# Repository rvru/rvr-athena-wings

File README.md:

# RVR Athena Wing Board
**Contributor(s):** Ethan Peck

**Contact(s):** edp2@rice.edu

## Overview
Wing boards will be a collection of boards that will expand the functionality of the base Athena Board in a variety of ways. Oscilloscopes, function generators, motor drivers, various sensors, and displays are some of the many boards planned for the future.

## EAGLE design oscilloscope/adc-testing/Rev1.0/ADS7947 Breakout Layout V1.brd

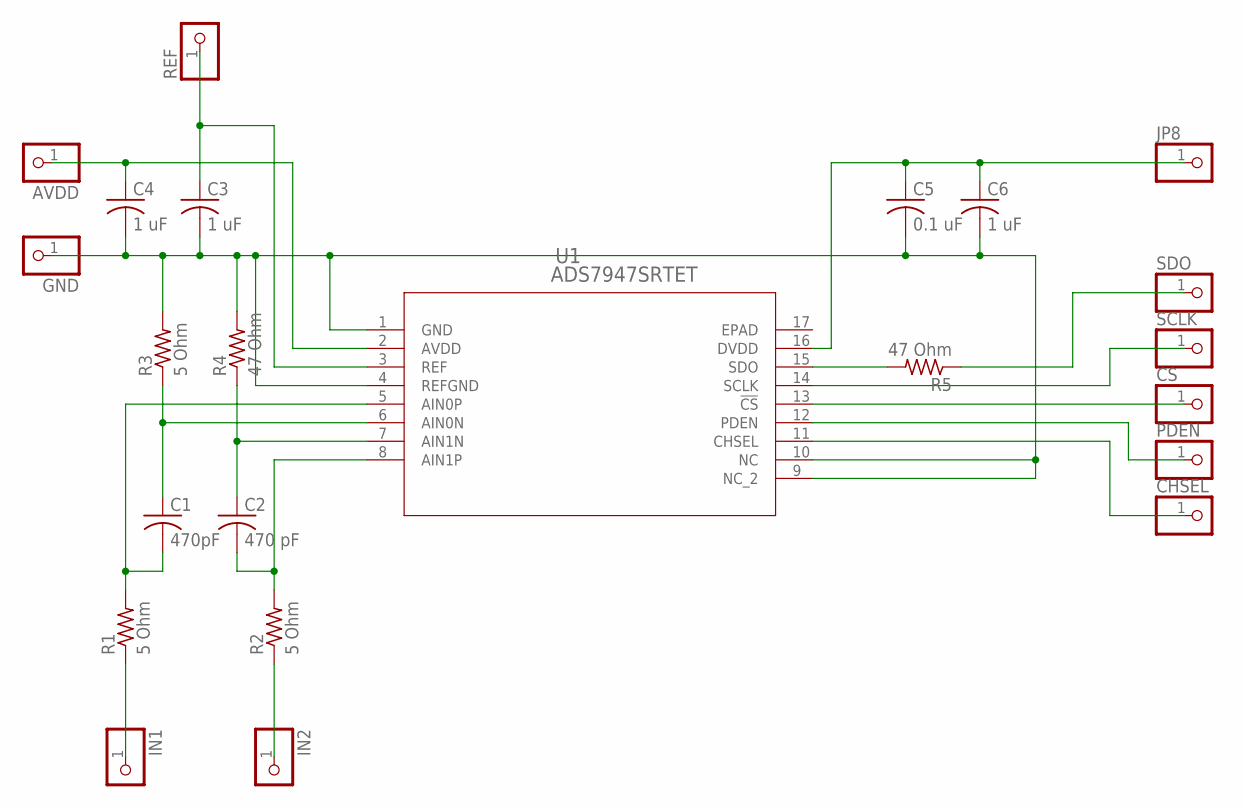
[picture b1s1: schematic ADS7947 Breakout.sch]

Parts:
AVDD: PINHD-1X1; 1X01
C1: 470pF; C1206
C2: 470 pF; C1206
C3, C4, C6: 1 uF; C1206
C5: 0.1 uF; C1206
CHSEL: PINHD-1X1; 1X01
CS: PINHD-1X1; 1X01
GND: PINHD-1X1; 1X01
IN1, IN2: PINHD-1X1; 1X01
JP8: PINHD-1X1; 1X01
PDEN: PINHD-1X1; 1X01
R1, R2, R3: 5 Ohm; R1206
R4, R5: 47 Ohm; R1206
REF: PINHD-1X1; 1X01
SCLK: PINHD-1X1; 1X01
SDO: PINHD-1X1; 1X01
U1: ADS7947SRTET; RTE16_1P7X1P7

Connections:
EPAD: U1.17 (EPAD)
GND: C3.2, C4.2, C5.2, C6.2, GND.1, R3.2, R4.2, U1.1 (GND), U1.4 (REFGND), U1.9 (NC_2), U1.10 (NC)
unnamed: IN2.1, R2.1
unnamed: C2.2, R2.2, U1.8 (AIN1P)
unnamed: C1.2, R1.2, U1.5 (AIN0P)
unnamed: IN1.1, R1.1
unnamed: C2.1, R4.1, U1.7 (AIN1N)
unnamed: C1.1, R3.1, U1.6 (AIN0N)
unnamed: C3.1, REF.1, U1.3 (REF)
unnamed: AVDD.1, C4.1, U1.2 (AVDD)
unnamed 13: C5.1, C6.1, JP8.1, U1.16 (DVDD); also elsewhere on the board
unnamed: R5.2, U1.15 (SDO)
unnamed: R5.1, SDO.1
unnamed: SCLK.1, U1.14 (SCLK)
unnamed: CS.1, U1.13 (!CS)
unnamed: PDEN.1, U1.12 (PDEN)
unnamed: CHSEL.1, U1.11 (CHSEL)

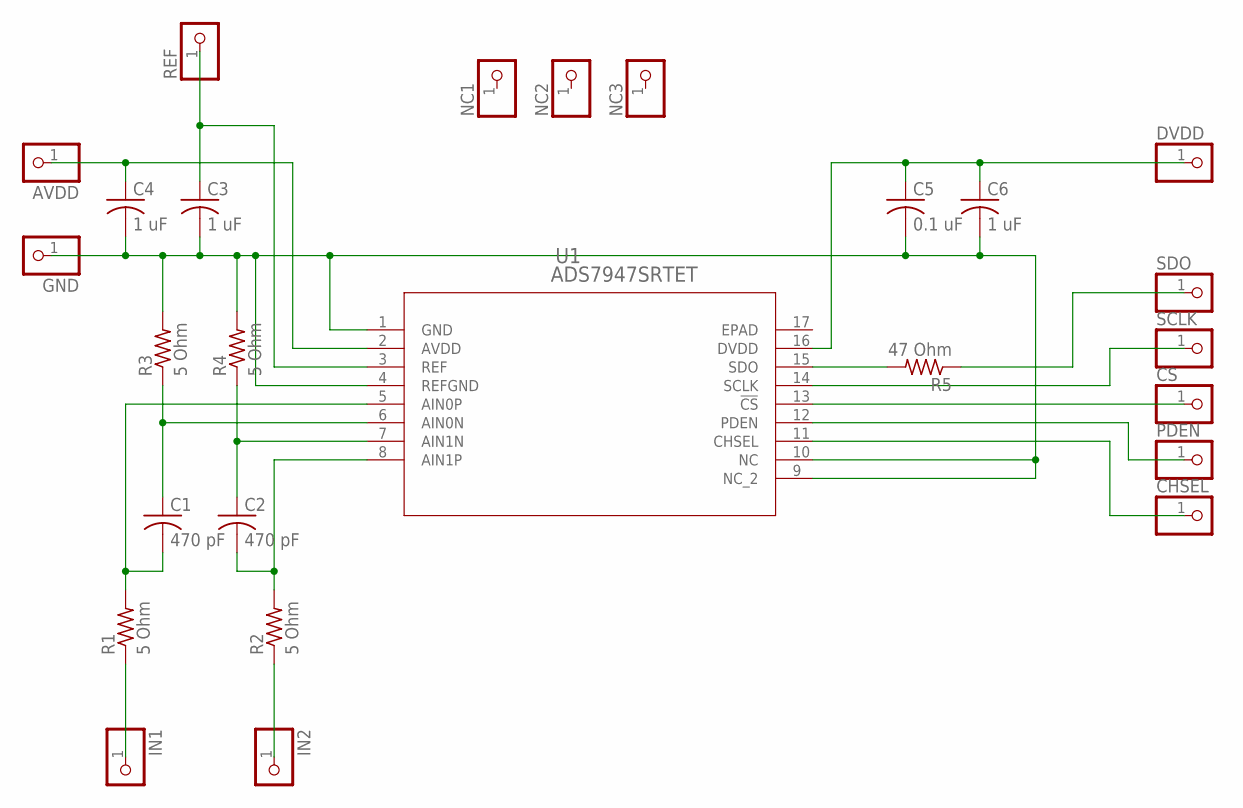
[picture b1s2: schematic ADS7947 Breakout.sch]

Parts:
AVDD: PINHD-1X1; 1X01
C1, C2: 470 pF; C0805
C3, C4, C6: 1 uF; C0805
C5: 0.1 uF; C0805
CHSEL: PINHD-1X1; 1X01
CS: PINHD-1X1; 1X01
DVDD: PINHD-1X1; 1X01
GND: PINHD-1X1; 1X01
IN1, IN2: PINHD-1X1; 1X01
NC1, NC2, NC3: PINHD-1X1; 1X01
PDEN: PINHD-1X1; 1X01
R1, R2, R3, R4: 5 Ohm; R0805
R5: 47 Ohm; R0805
REF: PINHD-1X1; 1X01
SCLK: PINHD-1X1; 1X01
SDO: PINHD-1X1; 1X01
U1: ADS7947SRTET; RTE16_1P7X1P7

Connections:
EPAD: U1.17 (EPAD)
GND: C3.2, C4.2, C5.2, C6.2, GND.1, R3.2, R4.2, U1.1 (GND), U1.4 (REFGND), U1.9 (NC_2), U1.10 (NC)
unnamed: IN2.1, R2.1
unnamed: C2.2, R2.2, U1.8 (AIN1P)
unnamed: C1.2, R1.2, U1.5 (AIN0P)
unnamed: IN1.1, R1.1
unnamed: C2.1, R4.1, U1.7 (AIN1N)
unnamed: C1.1, R3.1, U1.6 (AIN0N)
unnamed: C3.1, REF.1, U1.3 (REF)
unnamed: AVDD.1, C4.1, U1.2 (AVDD)
unnamed 13: C5.1, C6.1, DVDD.1, U1.16 (DVDD); also elsewhere on the board
unnamed: R5.2, U1.15 (SDO)
unnamed: R5.1, SDO.1
unnamed: SCLK.1, U1.14 (SCLK)
unnamed: CS.1, U1.13 (!CS)
unnamed: PDEN.1, U1.12 (PDEN)
unnamed: CHSEL.1, U1.11 (CHSEL)

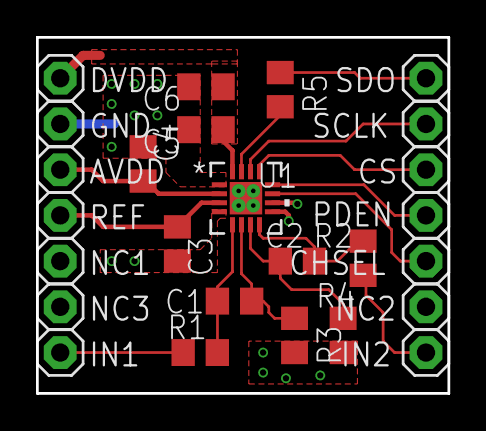
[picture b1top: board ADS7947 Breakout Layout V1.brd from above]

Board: 2 copper layers, 22.9 x 19.8 mm, 26 parts (0 on the bottom side), 16 nets.

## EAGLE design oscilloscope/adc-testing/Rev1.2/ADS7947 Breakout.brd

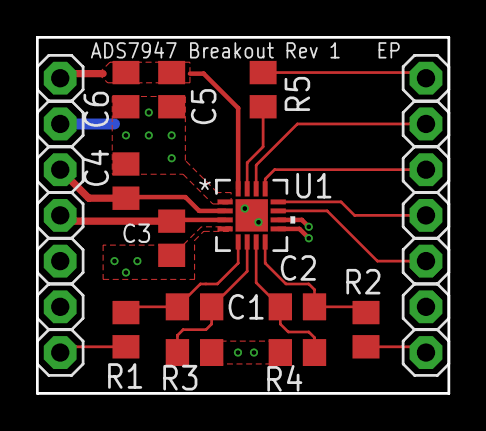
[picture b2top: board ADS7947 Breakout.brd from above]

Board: 2 copper layers, 22.9 x 19.8 mm, 26 parts (0 on the bottom side), 16 nets.

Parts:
AVDD: 1X01
C1, C2: 470pF; C0805
C3, C4, C5: 1uF; C0805
C6: 0.1uF; C0805
CHSEL: 1X01
CS: 1X01
DVDD: 1X01
GND: 1X01
IN0, IN1: 1X01
NC1, NC2, NC3: 1X01
PDEN: 1X01
R1, R2, R3, R4: 5 Ohm; R0805
R5: 47 Ohm; R0805
REF: 1X01
SCLK: 1X01
SDO: 1X01
U1: ADS7947SRTET; RTE16_1P7X1P7

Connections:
AIN0N: C1.2, R3.1, U1.6
AIN0P: C1.1, R1.2, U1.5
AIN1N: C2.2, R4.1, U1.7
AIN1P: C2.1, R2.2, U1.8
AVDD: AVDD.1, C4.2, U1.2
CHSEL: CHSEL.1, U1.11
CS: CS.1, U1.13
DVDD: C5.2, C6.2, DVDD.1, U1.16
GND: C3.1, C4.1, C5.1, C6.1, GND.1, R3.2, R4.2, U1.1, U1.4, U1.9, U1.10, U1.17
IN0: IN0.1, R1.1
IN1: IN1.1, R2.1
unnamed: R5.1, SDO.1
PDEN: PDEN.1, U1.12
REF: C3.2, REF.1, U1.3
SCLK: SCLK.1, U1.14
SDO: R5.2, U1.15

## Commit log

2021-06-25 AD7947 testing breakout board schematic
2021-06-27 Fixed schematic, added NC pins
2021-07-10 Board layout V1
2021-08-04 Revision 2 of ADS7947 breakout board.
2021-08-08 Final update to revision 1, update folder names to match revision
2021-10-11 Add project files for ADC expansion board, rename file
2021-10-12 Add switch for choosing between built in GND or REFGND
